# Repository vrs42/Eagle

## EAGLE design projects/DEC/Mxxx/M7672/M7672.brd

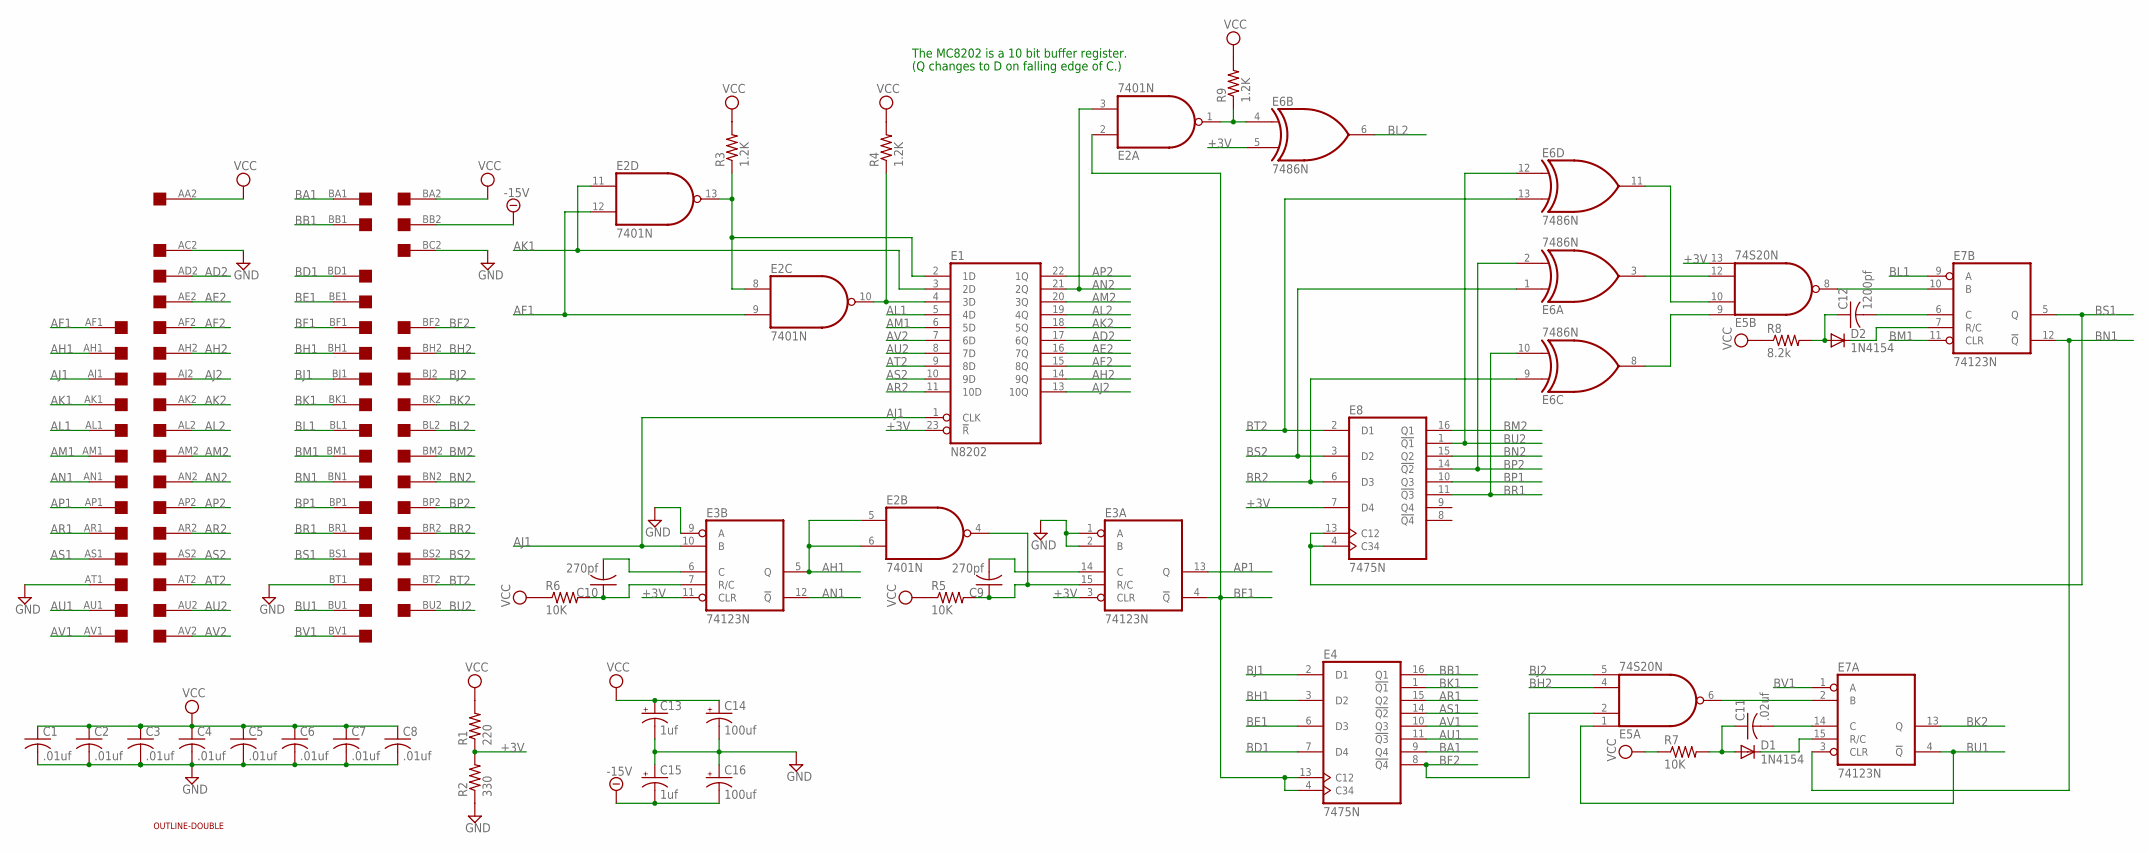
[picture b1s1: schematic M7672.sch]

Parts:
C1, C2, C3, C4, C5, C6, C7, C8: .01uf; C050-025X075
C9, C10: 270pf; C050-025X075
C11: .02uf; C050-025X075
C12: 1200pf; C050-025X075
C13, C15: 1uf; E30-10
C14, C16: 100uf; E30-10
D1, D2: 1N4154; DO35-10
E1: N8202; DIL24
E2: 7401N; DIL14
E3, E7: 74123N; DIL16
E4, E8: 7475N; DIL16
E5: 74S20N; DIL14
E6: 7486N; DIL14
EDGE: DOUBLE; EDGE-CON4
R1: 220; 0207/10
R2: 330; 0207/10
R3, R4, R9: 1.2K; 0207/10
R5, R6, R7: 10K; 0207/10
R8: 8.2k; 0207/10
U$2: OUTLINE-DOUBLE; DOUBLE

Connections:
+3V: E1.23 (!R), E3.3 (CLR), E3.11 (CLR), E5.13 (I3), E6.5 (I1), E8.7 (D4), R1.1, R2.2
-15V: C15.-, C16.-, EDGE.BB2
AD2: E1.17 (6Q), EDGE.AD2
AE2: E1.16 (7Q), EDGE.AE2
AF1: E2.9 (I1), E2.12 (I1), EDGE.AF1
AF2: E1.15 (8Q), EDGE.AF2
AH1: E2.5 (I0), E2.6 (I1), E3.5 (Q), EDGE.AH1
AH2: E1.14 (9Q), EDGE.AH2
AJ1: E1.1 (CLK), E3.10 (B), EDGE.AJ1
AJ2: E1.13 (10Q), EDGE.AJ2
AK1: E1.3 (2D), E2.11 (I0), EDGE.AK1
AK2: E1.18 (5Q), EDGE.AK2
AL1: E1.5 (4D), EDGE.AL1
AL2: E1.19 (4Q), EDGE.AL2
AM1: E1.6 (5D), EDGE.AM1
AM2: E1.20 (3Q), EDGE.AM2
AN1: E3.12 (!Q), EDGE.AN1
AN2: E1.21 (2Q), E2.3 (I1), EDGE.AN2
AP1: E3.13 (Q), EDGE.AP1
AP2: E1.22 (1Q), EDGE.AP2
AR1: E4.15 (Q2), EDGE.AR1
AR2: E1.11 (10D), EDGE.AR2
AS1: E4.14 (!Q2), EDGE.AS1
AS2: E1.10 (9D), EDGE.AS2
AT2: E1.9 (8D), EDGE.AT2
AU1: E4.11 (!Q3), EDGE.AU1
AU2: E1.8 (7D), EDGE.AU2
AV1: E4.10 (Q3), EDGE.AV1
AV2: E1.7 (6D), EDGE.AV2
BA1: E4.9 (Q4), EDGE.BA1
BB1: E4.16 (Q1), EDGE.BB1
BD1: E4.7 (D4), EDGE.BD1
BE1: E4.6 (D3), EDGE.BE1
BF1: E2.2 (I0), E3.4 (!Q), E4.4 (C34), E4.13 (C12), EDGE.BF1
BF2: E4.8 (!Q4), E5.2 (I1), EDGE.BF2
BH1: E4.3 (D2), EDGE.BH1
BH2: E5.4 (I2), EDGE.BH2
BJ1: E4.2 (D1), EDGE.BJ1
BJ2: E5.5 (I3), EDGE.BJ2
BK1: E4.1 (!Q1), EDGE.BK1
BK2: E7.13 (Q), EDGE.BK2
BL1: E7.9 (A), EDGE.BL1
BL2: E6.6 (O), EDGE.BL2
BM1: E7.11 (CLR), EDGE.BM1
BM2: E8.16 (Q1), EDGE.BM2
BN1: E7.3 (CLR), E7.12 (!Q), EDGE.BN1
BN2: E8.15 (Q2), EDGE.BN2
BP1: E8.10 (Q3), EDGE.BP1
BP2: E6.2 (I1), E8.14 (!Q2), EDGE.BP2
BR1: E6.10 (I1), E8.11 (!Q3), EDGE.BR1
BR2: E6.9 (I0), E8.6 (D3), EDGE.BR2
BS1: E7.5 (Q), E8.4 (C34), E8.13 (C12), EDGE.BS1
BS2: E6.1 (I0), E8.3 (D2), EDGE.BS2
BT2: E6.13 (I1), E8.2 (D1), EDGE.BT2
BU1: E5.1 (I0), E7.4 (!Q), EDGE.BU1
BU2: E6.12 (I0), E8.1 (!Q1), EDGE.BU2
BV1: E7.1 (A), EDGE.BV1
GND: C1.2, C2.2, C3.2, C4.2, C5.2, C6.2, C7.2, C8.2, C13.-, C14.-, C15.+, C16.+, E1.12 (GND), E2.7 (GND), E3.1 (A), E3.2 (B), E3.8 (GND), E3.9 (A), E4.12 (GND), E5.7 (GND), E6.7 (GND), E7.8 (GND), E8.12 (GND), EDGE.AC2, EDGE.AT1, EDGE.BC2, EDGE.BT1, R2.1
unnamed: E1.2 (1D), E2.8 (I0), E2.13 (O), R3.1
unnamed: E1.4 (3D), E2.10 (O), R4.1
unnamed: E2.1 (O), E6.4 (I0), R9.1
unnamed: E5.12 (I2), E6.3 (O)
unnamed: C10.1, E3.7 (R/C), R6.2
unnamed: C10.2, E3.6 (C)
unnamed: C9.1, E2.4 (O), E3.15 (R/C), R5.2
unnamed: C9.2, E3.14 (C)
unnamed: E5.10 (I1), E6.11 (O)
unnamed: E5.9 (I0), E6.8 (O)
unnamed: E5.6 (O), E7.2 (B)
unnamed: D1.C, E7.15 (R/C)
unnamed: C11.2, E7.14 (C)
unnamed: C11.1, D1.A, R7.2
unnamed: E5.8 (O), E7.10 (B)
unnamed: D2.C, E7.7 (R/C)
unnamed: C12.2, E7.6 (C)
unnamed: C12.1, D2.A, R8.2
VCC: C1.1, C2.1, C3.1, C4.1, C5.1, C6.1, C7.1, C8.1, C13.+, C14.+, E1.24 (VCC), E2.14 (VCC), E3.16 (VCC), E4.5 (VCC), E5.14 (VCC), E6.14 (VCC), E7.16 (VCC), E8.5 (VCC), EDGE.AA2, EDGE.BA2, R1.2, R3.2, R4.2, R5.1, R6.1, R7.1, R8.1, R9.2

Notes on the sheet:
The MC8202 is a 10 bit buffer register.
(Q changes to D on falling edge of C.)

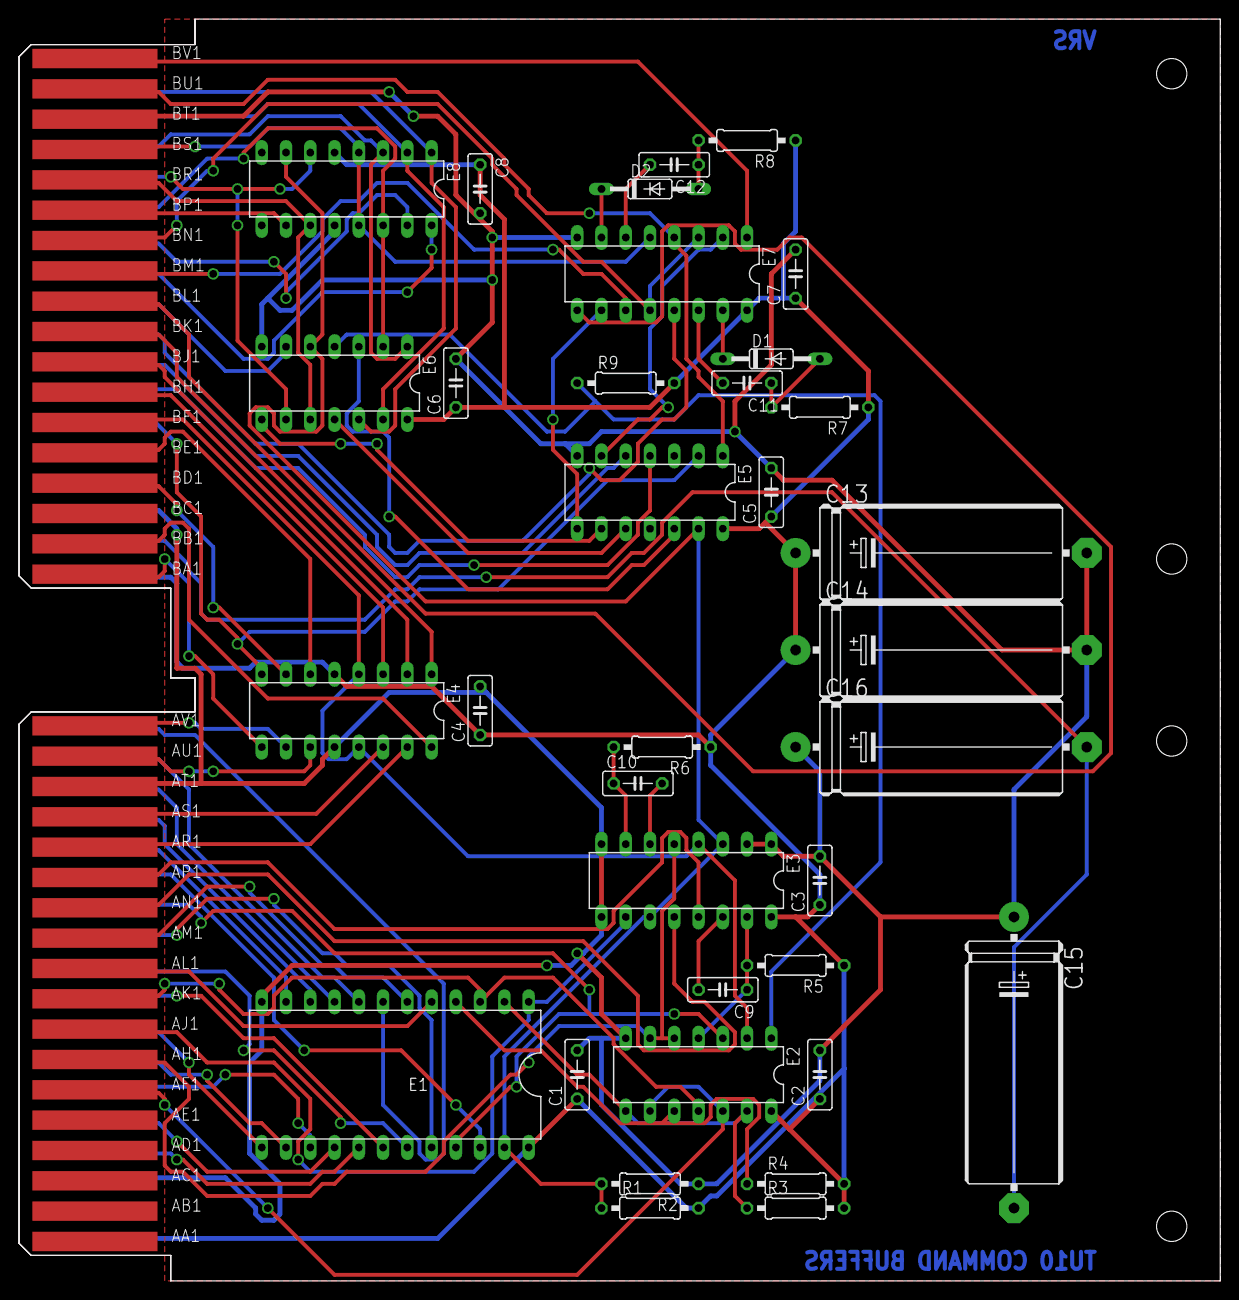
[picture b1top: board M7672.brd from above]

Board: 2 copper layers, 125.7 x 132.1 mm, 37 parts (0 on the bottom side), 77 nets.

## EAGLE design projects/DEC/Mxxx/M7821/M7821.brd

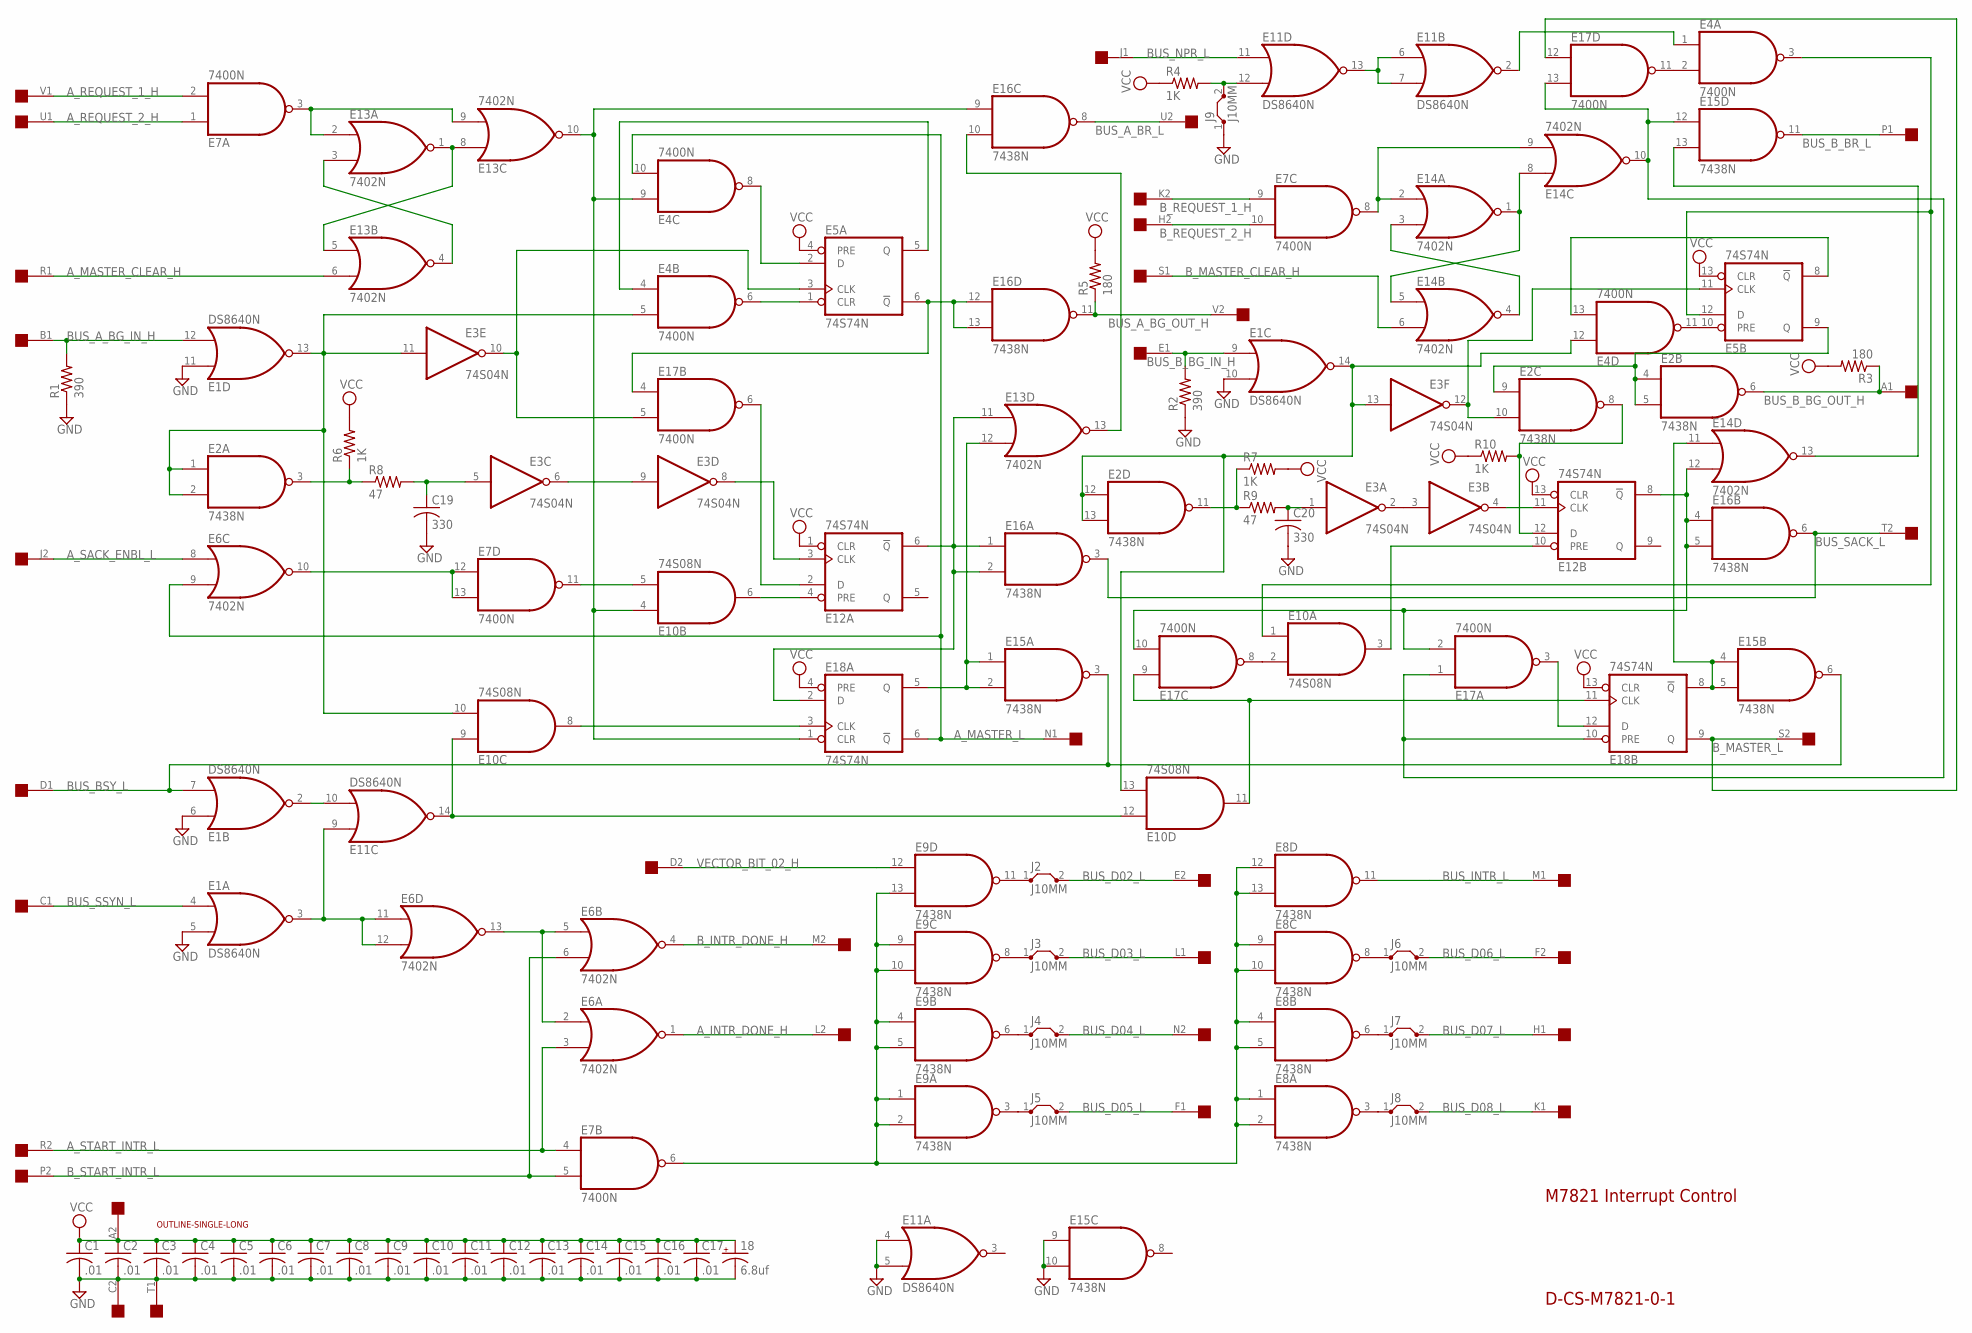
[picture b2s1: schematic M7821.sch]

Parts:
18: 6.8uf; E15-5
C1, C2, C3, C4, C5, C6, C7, C8, C9, C10, C11, C12, C13, C14, C15, C16, C17: .01; C050-025X075
C19, C20: 330; C050-025X075
E1, E11: DS8640N; DIL14
E2, E8, E9, E15, E16: 7438N; DIL14
E3: 74S04N; DIL14
E4, E7, E17: 7400N; DIL14
E5, E12, E18: 74S74N; DIL14
E6, E13, E14: 7402N; DIL14
E10: 74S08N; DIL14
J2, J3, J4, J5, J6, J7, J8, J9: J10MM; 10
R1, R2: 390; 0207/10
R3, R5: 180; 0207/10
R4, R6, R7, R10: 1K; 0207/10
R8, R9: 47; 0207/10
U$1: OUTLINE-SINGLE-LONG; SINGLE-LONG
U$2: SINGLE; EDGE-CON2

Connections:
A_INTR_DONE_H: E6.1 (O), U$2.L2
A_MASTER_CLEAR_H: E13.6 (I1), U$2.R1
A_MASTER_L: E4.10 (I1), E6.9 (I1), E18.6 (!Q), U$2.N1
A_REQUEST_1_H: E7.2 (I1), U$2.V1
A_REQUEST_2_H: E7.1 (I0), U$2.U1
A_SACK_ENBL_L: E6.8 (I0), U$2.J2
A_START_INTR_L: E6.3 (I1), E7.4 (I0), U$2.R2
BUS_A_BG_IN_H: E1.12 (I1), R1.2, U$2.B1
BUS_A_BG_OUT_H: E16.11 (O), R5.1, U$2.V2
BUS_A_BR_L: E16.8 (O), U$2.U2
BUS_BSY_L: E1.7 (I1), E15.3 (O), E15.6 (O), U$2.D1
BUS_B_BG_IN_H: E1.9 (I0), R2.2, U$2.E1
BUS_B_BG_OUT_H: E2.6 (O), R3.1, U$2.A1
BUS_B_BR_L: E15.11 (O), U$2.P1
BUS_D02_L: J2.2, U$2.E2
BUS_D03_L: J3.2, U$2.L1
BUS_D04_L: J4.2, U$2.N2
BUS_D05_L: J5.2, U$2.F1
BUS_D06_L: J6.2, U$2.F2
BUS_D07_L: J7.2, U$2.H1
BUS_D08_L: J8.2, U$2.K1
BUS_INTR_L: E8.11 (O), U$2.M1
BUS_NPR_L: E11.11 (I0), U$2.J1
BUS_SACK_L: E16.3 (O), E16.6 (O), U$2.T2
BUS_SSYN_L: E1.4 (I0), U$2.C1
B_INTR_DONE_H: E6.4 (O), U$2.M2
B_MASTER_CLEAR_H: E14.6 (I1), U$2.S1
B_MASTER_L: E17.12 (I0), E18.9 (Q), U$2.S2
B_REQUEST_1_H: E7.9 (I0), U$2.K2
B_REQUEST_2_H: E7.10 (I1), U$2.H2
B_START_INTR_L: E6.6 (I1), E7.5 (I1), U$2.P2
GND: 18.-, C1.2, C2.2, C3.2, C4.2, C5.2, C6.2, C7.2, C8.2, C9.2, C10.2, C11.2, C12.2, C13.2, C14.2, C15.2, C16.2, C17.2, C19.2, C20.2, E1.1 (GND), E1.5 (I1), E1.6 (I0), E1.10 (I1), E1.11 (I0), E2.7 (GND), E3.7 (GND), E4.7 (GND), E5.7 (GND), E6.7 (GND), E7.7 (GND), E8.7 (GND), E9.7 (GND), E10.7 (GND), E11.1 (GND), E11.4 (I0), E11.5 (I1), E12.7 (GND), E13.7 (GND), E14.7 (GND), E15.7 (GND), E15.9 (I0), E15.10 (I1), E16.7 (GND), E17.7 (GND), E18.7 (GND), J9.1, R1.1, R2.1, U$2.C2, U$2.T1
unnamed: E1.14 (O), E2.12 (I0), E2.13 (I1), E3.13 (I), E4.12 (I0), E10.13 (I1)
unnamed: E1.13 (O), E2.1 (I0), E2.2 (I1), E3.11 (I), E4.5 (I1), E10.10 (I1)
unnamed: E1.3 (O), E6.11 (I0), E6.12 (I1), E11.9 (I0)
unnamed: E1.2 (O), E11.10 (I1)
unnamed: E7.8 (O), E14.2 (I0), E14.9 (I1)
unnamed: E11.12 (I1), J9.2, R4.2
unnamed: E11.6 (I0), E11.7 (I1), E11.13 (O)
unnamed: E6.10 (O), E7.12 (I0), E7.13 (I1)
unnamed: E14.3 (I1), E14.4 (O)
unnamed: E9.11 (O), J2.1
unnamed: E3.8 (O), E12.3 (CLK)
unnamed: E7.11 (O), E10.5 (I1)
unnamed: E4.13 (I1), E5.8 (!Q)
unnamed: E14.1 (O), E14.5 (I0), E14.8 (I0)
unnamed: E2.11 (O), R7.1, R9.1
unnamed: E9.3 (O), J5.1
unnamed: E9.6 (O), J4.1
unnamed: E9.8 (O), J3.1
unnamed: E10.9 (I0), E10.12 (I0), E11.14 (O)
unnamed: E8.3 (O), J8.1
unnamed: E8.6 (O), J7.1
unnamed: E8.8 (O), J6.1
unnamed: E7.6 (O), E8.1 (I0), E8.2 (I1), E8.4 (I0), E8.5 (I1), E8.9 (I0), E8.10 (I1), E8.12 (I0), E8.13 (I1), E9.1 (I0), E9.2 (I1), E9.4 (I0), E9.5 (I1), E9.9 (I0), E9.10 (I1), E9.13 (I1)
unnamed: E12.6 (!Q), E13.11 (I0), E16.1 (I0), E16.2 (I1), E18.2 (D)
unnamed: E13.12 (I1), E15.1 (I0), E15.2 (I1), E18.5 (Q)
unnamed: E4.6 (O), E5.1 (CLR)
unnamed: E4.8 (O), E5.2 (D)
unnamed: E4.4 (I0), E5.5 (Q)
unnamed: E3.10 (O), E5.3 (CLK), E17.5 (I1)
unnamed: E12.2 (D), E17.6 (O)
unnamed: E5.6 (!Q), E16.12 (I0), E16.13 (I1), E17.4 (I0)
unnamed: E13.13 (O), E16.10 (I1)
unnamed: C20.1, E3.1 (I), R9.2
unnamed: E6.2 (I0), E6.5 (I0), E6.13 (O)
unnamed: E3.2 (O), E3.3 (I)
unnamed: E3.4 (O), E12.11 (CLK)
unnamed: E10.6 (O), E12.4 (PRE)
unnamed: E2.3 (O), R6.1, R8.1
unnamed: C19.1, E3.5 (I), R8.2
unnamed: E3.6 (O), E3.9 (I)
unnamed: E10.11 (O), E17.9 (I0), E18.11 (CLK)
unnamed: E7.3 (O), E13.2 (I0), E13.9 (I1)
unnamed: E13.1 (O), E13.5 (I0), E13.8 (I0)
unnamed: E13.3 (I1), E13.4 (O)
unnamed: E4.9 (I0), E10.4 (I0), E13.10 (O), E16.9 (I0), E18.1 (CLR)
unnamed: E10.8 (O), E18.3 (CLK)
unnamed: E4.1 (I0), E11.2 (O)
unnamed: E14.11 (I0), E15.4 (I0), E15.5 (I1), E18.8 (!Q)
unnamed: E17.3 (O), E18.12 (D)
unnamed: E14.10 (O), E15.12 (I0), E17.1 (I0), E17.13 (I1), E18.10 (PRE)
unnamed: E10.2 (I1), E17.8 (O)
unnamed: E12.8 (!Q), E14.12 (I1), E16.4 (I0), E16.5 (I1), E17.2 (I1), E17.10 (I1)
unnamed: E10.3 (O), E12.10 (PRE)
unnamed: E4.3 (O), E5.12 (D), E10.1 (I0)
unnamed: E2.8 (O), E12.12 (D), R10.2
unnamed: E2.10 (I1), E3.12 (O), E5.11 (CLK)
unnamed: E2.4 (I0), E2.5 (I1), E2.9 (I0), E5.9 (Q)
unnamed: E4.11 (O), E5.10 (PRE)
unnamed: E4.2 (I1), E17.11 (O)
unnamed: E14.13 (O), E15.13 (I1)
VCC: 18.+, C1.1, C2.1, C3.1, C4.1, C5.1, C6.1, C7.1, C8.1, C9.1, C10.1, C11.1, C12.1, C13.1, C14.1, C15.1, C16.1, C17.1, E1.8 (VCC), E2.14 (VCC), E3.14 (VCC), E4.14 (VCC), E5.4 (PRE), E5.13 (CLR), E5.14 (VCC), E6.14 (VCC), E7.14 (VCC), E8.14 (VCC), E9.14 (VCC), E10.14 (VCC), E11.8 (VCC), E12.1 (CLR), E12.13 (CLR), E12.14 (VCC), E13.14 (VCC), E14.14 (VCC), E15.14 (VCC), E16.14 (VCC), E17.14 (VCC), E18.4 (PRE), E18.13 (CLR), E18.14 (VCC), R3.2, R4.1, R5.2, R6.2, R7.2, R10.1, U$2.A2
VECTOR_BIT_02_H: E9.12 (I0), U$2.D2

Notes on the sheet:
M7821 Interrupt Control
D-CS-M7821-0-1

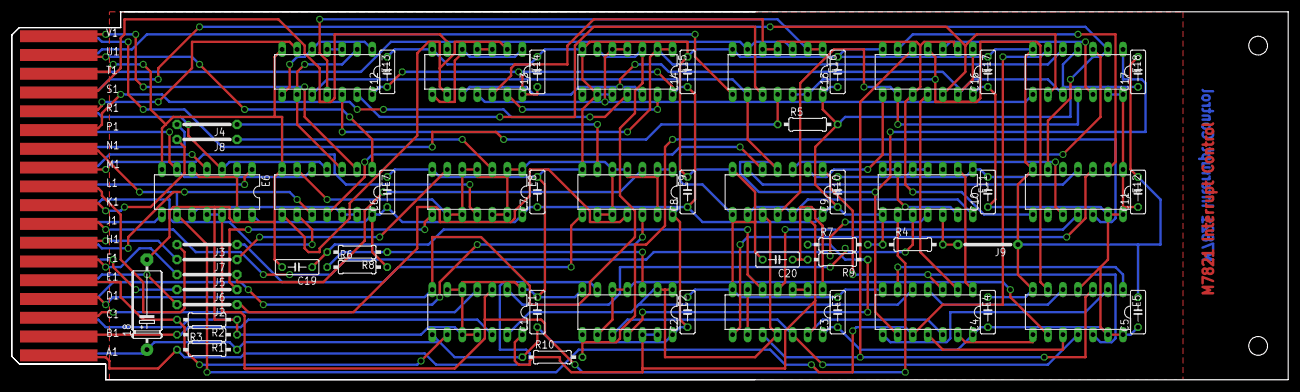
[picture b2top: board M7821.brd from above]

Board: 2 copper layers, 215.9 x 62.2 mm, 58 parts (0 on the bottom side), 94 nets.

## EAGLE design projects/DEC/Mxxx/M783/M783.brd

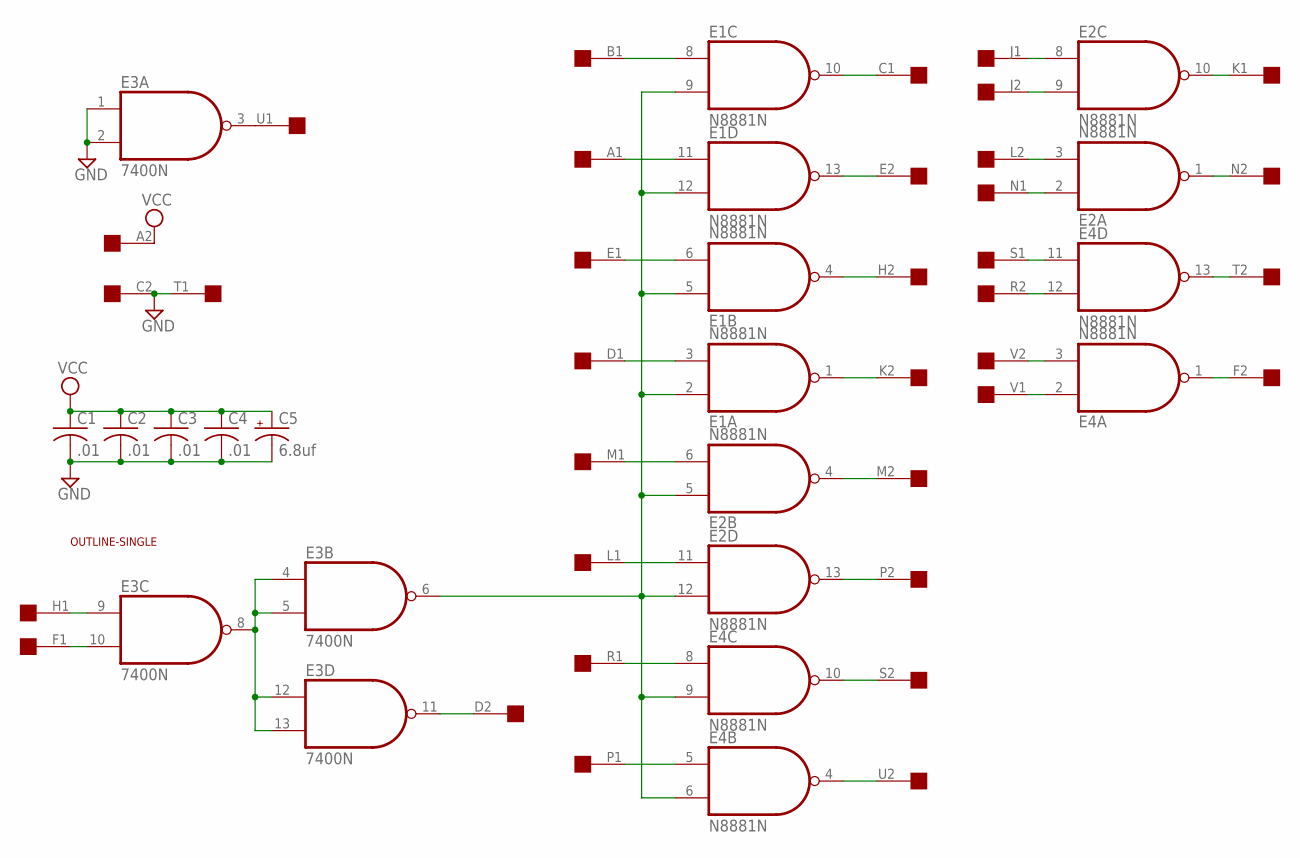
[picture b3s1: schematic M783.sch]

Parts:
C1, C2, C3, C4: .01; C050-025X075
C5: 6.8uf; E15-5
E1, E2, E4: N8881N; DIL14
E3: 7400N; DIL14
U$1: SINGLE; EDGE-CON2
U$2: OUTLINE-SINGLE; SINGLE

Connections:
GND: C1.2, C2.2, C3.2, C4.2, C5.-, E1.7 (GND), E2.7 (GND), E3.1 (I0), E3.2 (I1), E3.7 (GND), E4.7 (GND), U$1.C2, U$1.T1
unnamed: E3.3 (O), U$1.U1
unnamed: E1.2 (I0), E1.5 (I0), E1.9 (I1), E1.12 (I1), E2.5 (I0), E2.12 (I1), E3.6 (O), E4.6 (I1), E4.9 (I1)
unnamed: E2.4 (O), U$1.M2
unnamed: E2.13 (O), U$1.P2
unnamed: E4.5 (I0), U$1.P1
unnamed: E4.8 (I0), U$1.R1
unnamed: E4.10 (O), U$1.S2
unnamed: E2.11 (I0), U$1.L1
unnamed: E4.4 (O), U$1.U2
unnamed: E2.6 (I1), U$1.M1
unnamed: E1.10 (O), U$1.C1
unnamed: E1.8 (I0), U$1.B1
unnamed: E1.13 (O), U$1.E2
unnamed: E1.11 (I0), U$1.A1
unnamed: E1.4 (O), U$1.H2
unnamed: E1.6 (I1), U$1.E1
unnamed: E1.1 (O), U$1.K2
unnamed: E1.3 (I1), U$1.D1
unnamed: E3.11 (O), U$1.D2
unnamed: E4.1 (O), U$1.F2
unnamed: E4.13 (O), U$1.T2
unnamed: E2.1 (O), U$1.N2
unnamed: E2.10 (O), U$1.K1
unnamed: E2.8 (I0), U$1.J1
unnamed: E2.9 (I1), U$1.J2
unnamed: E2.3 (I1), U$1.L2
unnamed: E2.2 (I0), U$1.N1
unnamed: E4.11 (I0), U$1.S1
unnamed: E4.12 (I1), U$1.R2
unnamed: E3.4 (I0), E3.5 (I1), E3.8 (O), E3.12 (I0), E3.13 (I1)
unnamed: E3.9 (I0), U$1.H1
unnamed: E3.10 (I1), U$1.F1
unnamed: E4.3 (I1), U$1.V2
unnamed: E4.2 (I0), U$1.V1
VCC: C1.1, C2.1, C3.1, C4.1, C5.+, E1.14 (VCC), E2.14 (VCC), E3.14 (VCC), E4.14 (VCC), U$1.A2

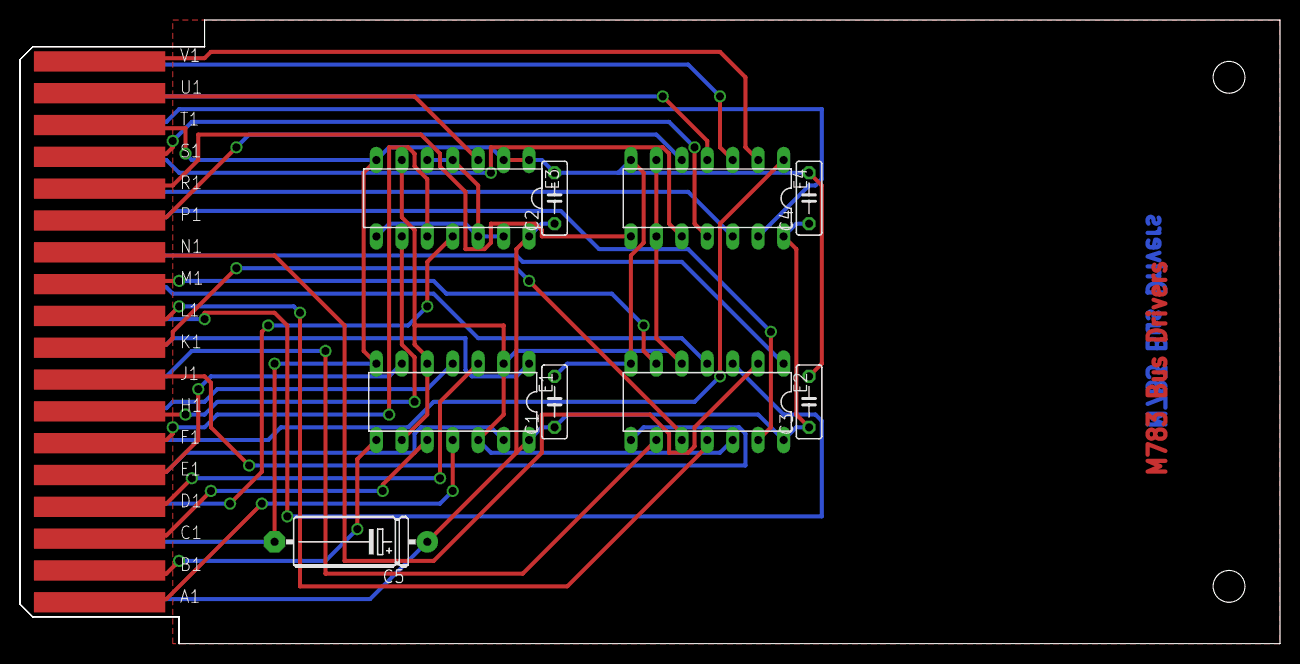
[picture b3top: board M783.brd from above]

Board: 2 copper layers, 125.7 x 62.2 mm, 11 parts (0 on the bottom side), 36 nets.

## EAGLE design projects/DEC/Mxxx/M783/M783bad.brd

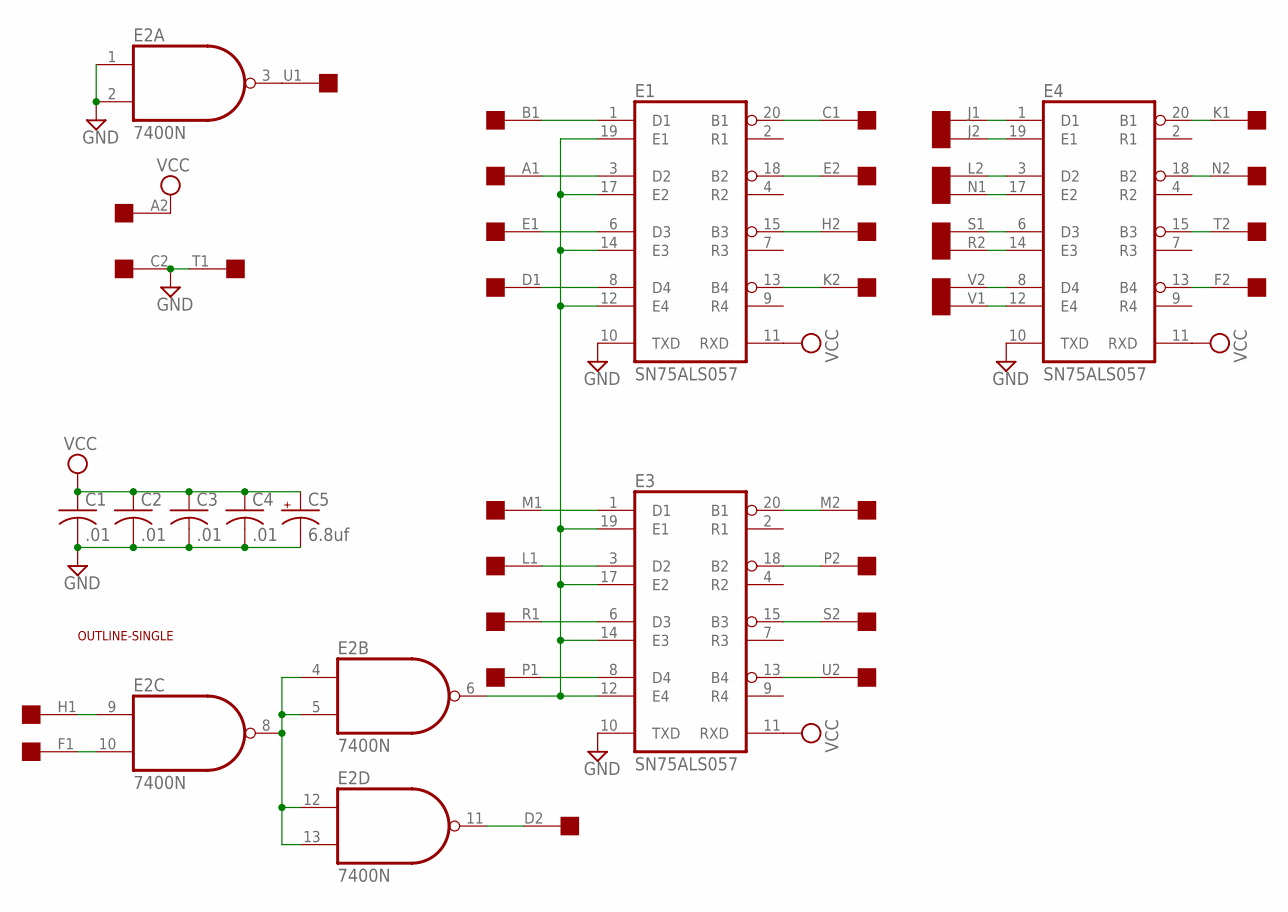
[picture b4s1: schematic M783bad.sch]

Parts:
C1, C2, C3, C4: .01; C050-025X075
C5: 6.8uf; E15-5
E1, E3, E4: SN75ALS057; DIL20
E2: 7400N; DIL14
U$1: SINGLE; EDGE-CON2
U$2: OUTLINE-SINGLE; SINGLE

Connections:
GND: C1.2, C2.2, C3.2, C4.2, C5.-, E1.10 (TXD), E1.16 (GND), E2.1 (I0), E2.2 (I1), E2.7 (GND), E3.10 (TXD), E3.16 (GND), E4.10 (TXD), E4.16 (GND), U$1.C2, U$1.T1
unnamed: E2.3 (O), U$1.U1
unnamed: E1.12 (E4), E1.14 (E3), E1.17 (E2), E1.19 (E1), E2.6 (O), E3.12 (E4), E3.14 (E3), E3.17 (E2), E3.19 (E1)
unnamed: E3.20 (B1), U$1.M2
unnamed: E3.18 (B2), U$1.P2
unnamed: E3.8 (D4), U$1.P1
unnamed: E3.6 (D3), U$1.R1
unnamed: E3.15 (B3), U$1.S2
unnamed: E3.3 (D2), U$1.L1
unnamed: E3.13 (B4), U$1.U2
unnamed: E3.1 (D1), U$1.M1
unnamed: E1.20 (B1), U$1.C1
unnamed: E1.1 (D1), U$1.B1
unnamed: E1.18 (B2), U$1.E2
unnamed: E1.3 (D2), U$1.A1
unnamed: E1.15 (B3), U$1.H2
unnamed: E1.6 (D3), U$1.E1
unnamed: E1.13 (B4), U$1.K2
unnamed: E1.8 (D4), U$1.D1
unnamed: E2.11 (O), U$1.D2
unnamed: E4.13 (B4), U$1.F2
unnamed: E4.15 (B3), U$1.T2
unnamed: E4.18 (B2), U$1.N2
unnamed: E4.20 (B1), U$1.K1
unnamed: E4.1 (D1), U$1.J1
unnamed: E4.19 (E1), U$1.J2
unnamed: E4.3 (D2), U$1.L2
unnamed: E4.17 (E2), U$1.N1
unnamed: E4.6 (D3), U$1.S1
unnamed: E4.14 (E3), U$1.R2
unnamed: E2.4 (I0), E2.5 (I1), E2.8 (O), E2.12 (I0), E2.13 (I1)
unnamed: E2.9 (I0), U$1.H1
unnamed: E2.10 (I1), U$1.F1
unnamed: E4.8 (D4), U$1.V2
unnamed: E4.12 (E4), U$1.V1
VCC: C1.1, C2.1, C3.1, C4.1, C5.+, E1.5 (VCC), E1.11 (RXD), E2.14 (VCC), E3.5 (VCC), E3.11 (RXD), E4.5 (VCC), E4.11 (RXD), U$1.A2

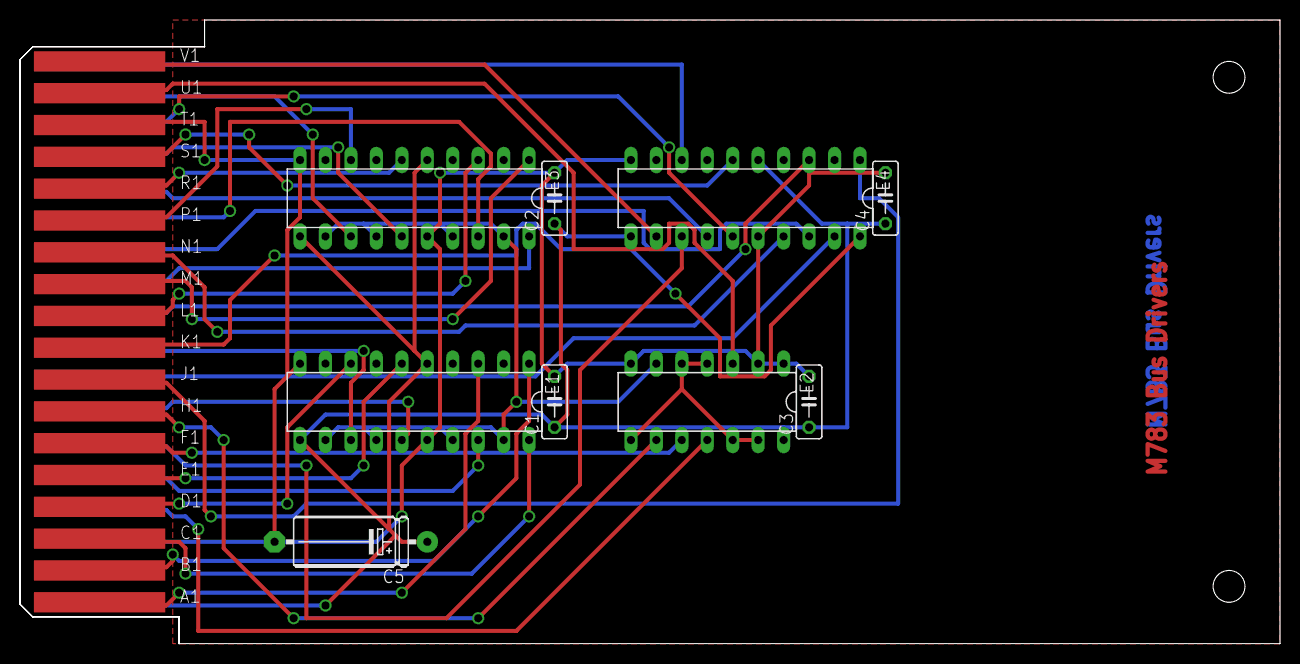
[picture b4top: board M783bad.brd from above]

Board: 2 copper layers, 125.7 x 62.2 mm, 11 parts (0 on the bottom side), 36 nets.

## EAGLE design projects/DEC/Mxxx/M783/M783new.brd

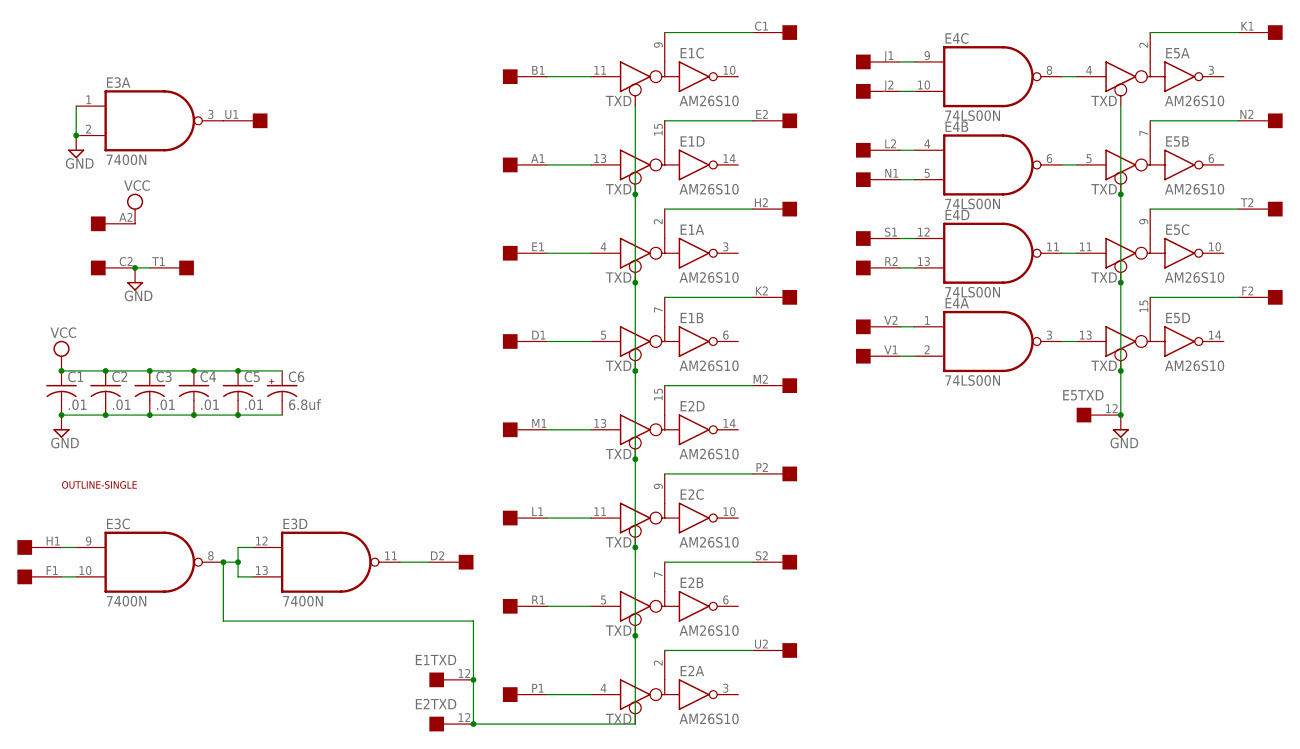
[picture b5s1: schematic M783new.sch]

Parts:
C1, C2, C3, C4, C5: .01; C050-025X075
C6: 6.8uf; E15-5
E1, E2, E5: AM26S10; DIL16
E3: 7400N; DIL14
E4: 74LS00N; DIL14
U$1: SINGLE; EDGE-CON2
U$2: OUTLINE-SINGLE; SINGLE

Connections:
GND: C1.2, C2.2, C3.2, C4.2, C5.2, C6.-, E1.1 (GND), E1.8 (GND), E2.1 (GND), E2.8 (GND), E3.1 (I0), E3.2 (I1), E3.7 (GND), E4.7 (GND), E5.1 (GND), E5.8 (GND), E5.12 (TXD), U$1.C2, U$1.T1
unnamed: E3.3 (O), U$1.U1
unnamed: E1.12 (TXD), E2.12 (TXD), E3.8 (O), E3.12 (I0), E3.13 (I1)
unnamed: E2.15 (B), U$1.M2
unnamed: E2.9 (B), U$1.P2
unnamed: E2.4 (D), U$1.P1
unnamed: E2.5 (D), U$1.R1
unnamed: E2.7 (B), U$1.S2
unnamed: E2.11 (D), U$1.L1
unnamed: E2.2 (B), U$1.U2
unnamed: E2.13 (D), U$1.M1
unnamed: E1.9 (B), U$1.C1
unnamed: E1.11 (D), U$1.B1
unnamed: E1.15 (B), U$1.E2
unnamed: E1.13 (D), U$1.A1
unnamed: E1.2 (B), U$1.H2
unnamed: E1.4 (D), U$1.E1
unnamed: E1.7 (B), U$1.K2
unnamed: E1.5 (D), U$1.D1
unnamed: E3.11 (O), U$1.D2
unnamed: E5.7 (B), U$1.N2
unnamed: E5.9 (B), U$1.T2
unnamed: E5.15 (B), U$1.F2
unnamed: E5.2 (B), U$1.K1
unnamed: E4.9 (I0), U$1.J1
unnamed: E4.10 (I1), U$1.J2
unnamed: E4.4 (I0), U$1.L2
unnamed: E4.5 (I1), U$1.N1
unnamed: E4.12 (I0), U$1.S1
unnamed: E4.13 (I1), U$1.R2
unnamed: E3.9 (I0), U$1.H1
unnamed: E3.10 (I1), U$1.F1
unnamed: E4.1 (I0), U$1.V2
unnamed: E4.2 (I1), U$1.V1
unnamed: E4.8 (O), E5.4 (D)
unnamed: E4.6 (O), E5.5 (D)
unnamed: E4.11 (O), E5.11 (D)
unnamed: E4.3 (O), E5.13 (D)
VCC: C1.1, C2.1, C3.1, C4.1, C5.1, C6.+, E1.16 (VCC), E2.16 (VCC), E3.14 (VCC), E4.14 (VCC), E5.16 (VCC), U$1.A2

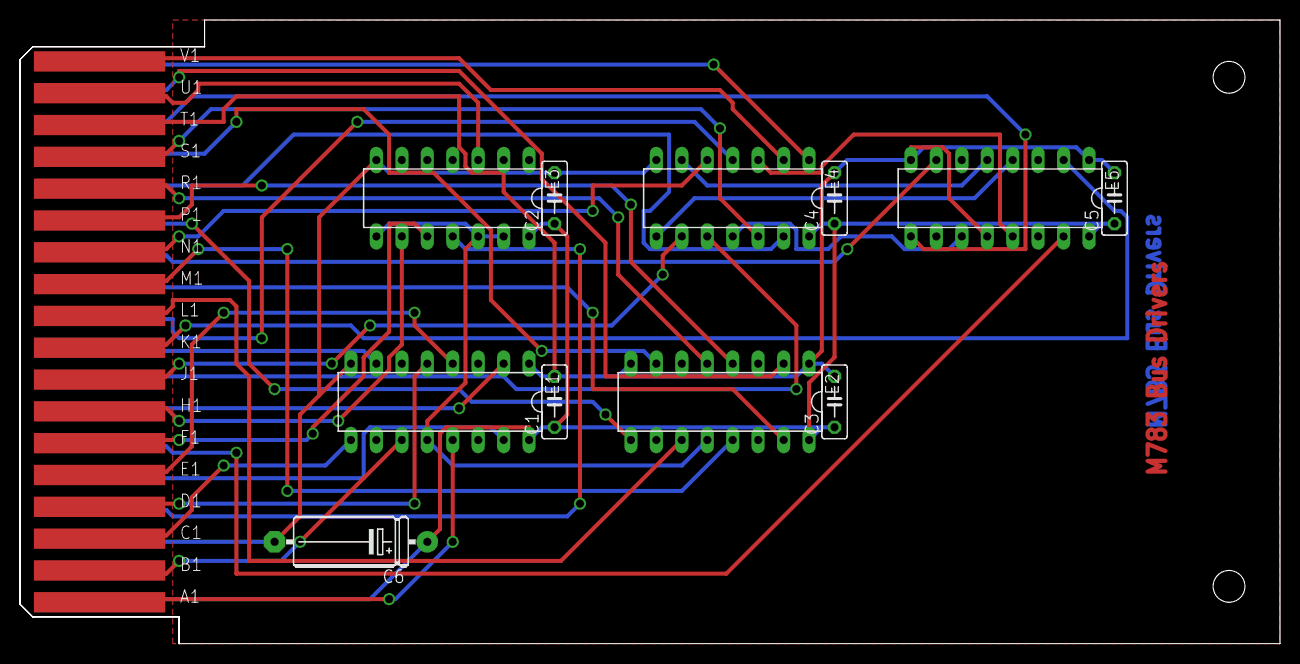
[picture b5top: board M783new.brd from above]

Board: 2 copper layers, 125.7 x 62.2 mm, 13 parts (0 on the bottom side), 39 nets.

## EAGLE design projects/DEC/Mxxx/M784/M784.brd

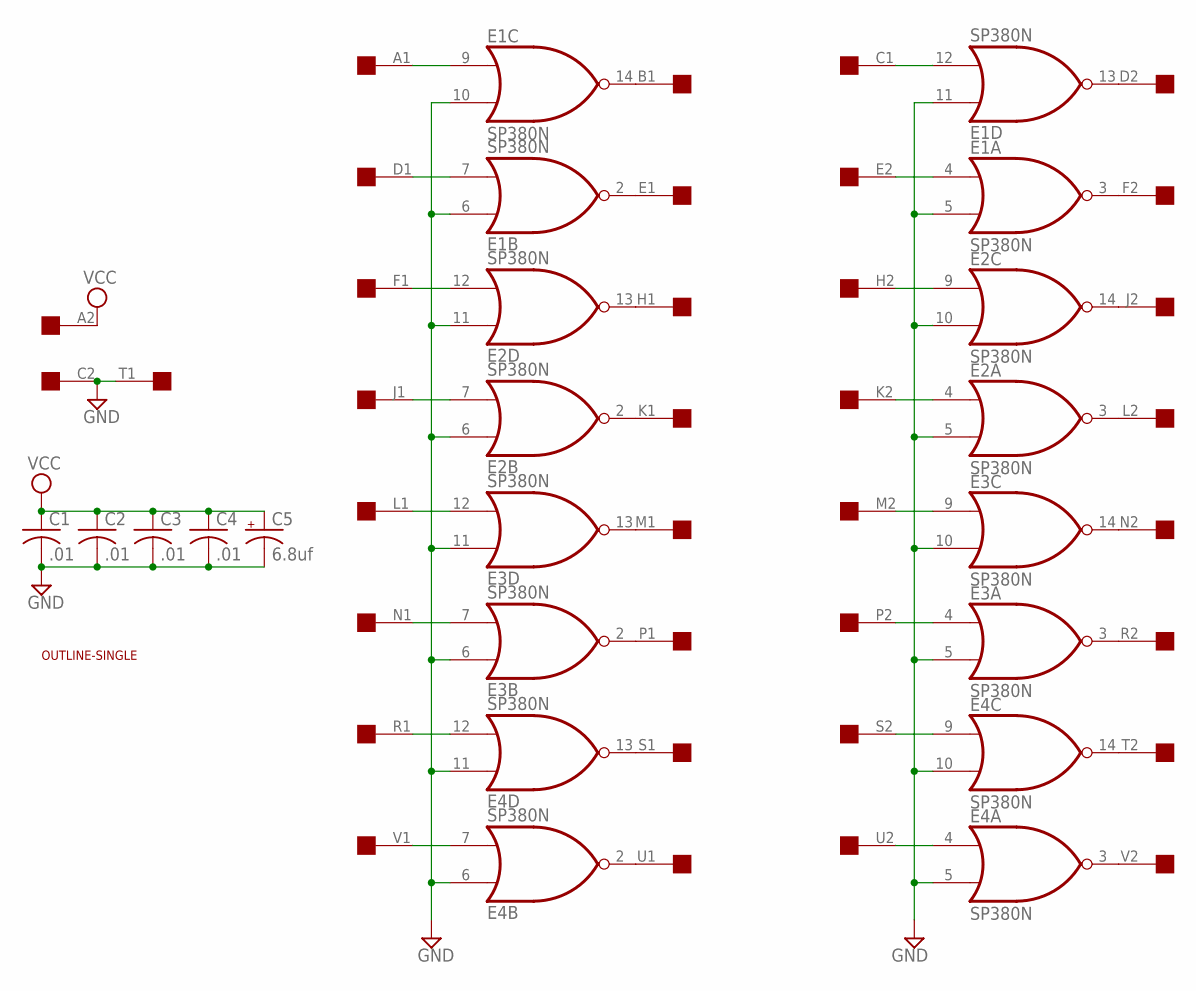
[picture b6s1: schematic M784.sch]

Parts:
C1, C2, C3, C4: .01; C050-025X075
C5: 6.8uf; E15-5
E1, E2, E3, E4: SP380N; DIL14
U$1: SINGLE; EDGE-CON2
U$2: OUTLINE-SINGLE; SINGLE

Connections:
GND: C1.2, C2.2, C3.2, C4.2, C5.-, E1.1 (GND), E1.5 (I1), E1.6 (I0), E1.10 (I1), E1.11 (I0), E2.1 (GND), E2.5 (I1), E2.6 (I0), E2.10 (I1), E2.11 (I0), E3.1 (GND), E3.5 (I1), E3.6 (I0), E3.10 (I1), E3.11 (I0), E4.1 (GND), E4.5 (I1), E4.6 (I0), E4.10 (I1), E4.11 (I0), U$1.C2, U$1.T1
unnamed: E3.13 (O), U$1.M1
unnamed: E3.12 (I1), U$1.L1
unnamed: E1.4 (I0), U$1.E2
unnamed: E1.3 (O), U$1.F2
unnamed: E3.7 (I1), U$1.N1
unnamed: E2.13 (O), U$1.H1
unnamed: E2.4 (I0), U$1.K2
unnamed: E1.2 (O), U$1.E1
unnamed: E2.7 (I1), U$1.J1
unnamed: E4.2 (O), U$1.U1
unnamed: E2.2 (O), U$1.K1
unnamed: E4.7 (I1), U$1.V1
unnamed: E3.2 (O), U$1.P1
unnamed: E1.13 (O), U$1.D2
unnamed: E4.12 (I1), U$1.R1
unnamed: E4.13 (O), U$1.S1
unnamed: E1.12 (I1), U$1.C1
unnamed: E2.3 (O), U$1.L2
unnamed: E2.14 (O), U$1.J2
unnamed: E2.9 (I0), U$1.H2
unnamed: E3.14 (O), U$1.N2
unnamed: E3.3 (O), U$1.R2
unnamed: E4.14 (O), U$1.T2
unnamed: E4.3 (O), U$1.V2
unnamed: E1.14 (O), U$1.B1
unnamed: E3.9 (I0), U$1.M2
unnamed: E3.4 (I0), U$1.P2
unnamed: E2.12 (I1), U$1.F1
unnamed: E4.9 (I0), U$1.S2
unnamed: E1.7 (I1), U$1.D1
unnamed: E4.4 (I0), U$1.U2
unnamed: E1.9 (I0), U$1.A1
VCC: C1.1, C2.1, C3.1, C4.1, C5.+, E1.8 (VCC), E2.8 (VCC), E3.8 (VCC), E4.8 (VCC), U$1.A2
